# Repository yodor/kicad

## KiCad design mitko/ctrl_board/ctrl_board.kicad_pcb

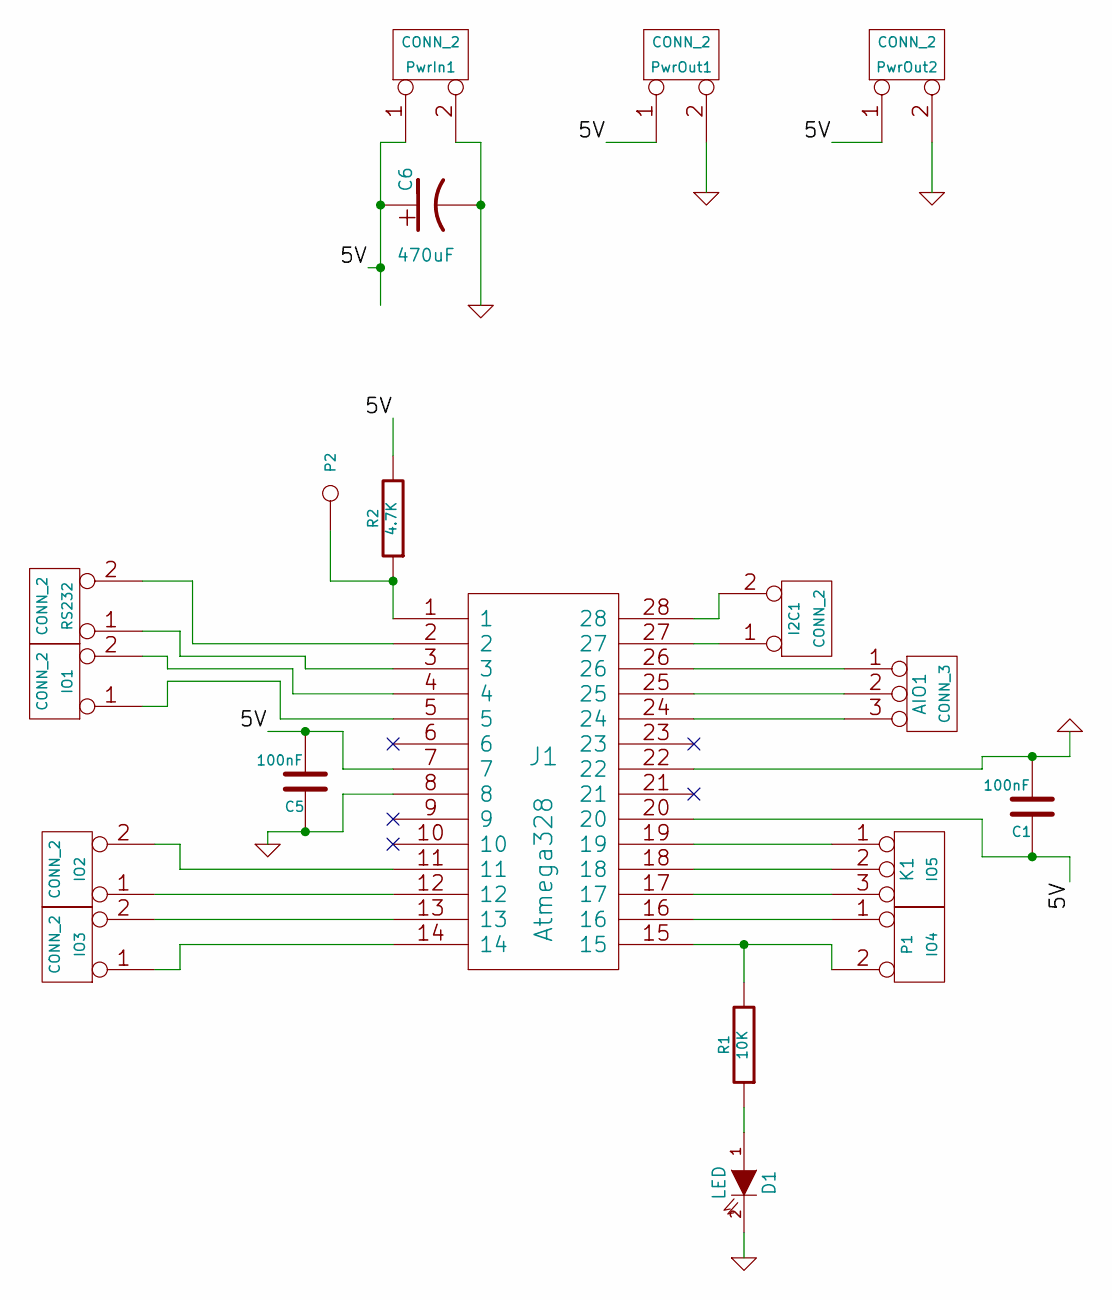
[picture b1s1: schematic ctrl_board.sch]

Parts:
AIO1: CONN_3
C1, C5: 100nF
C6: 470uF
D1: LED
I2C1: CONN_2
IO1, IO2, IO3: CONN_2
J1: Atmega328
K1: IO5
P1: IO4
P2: CONN_1
PwrIn1: CONN_2
PwrOut1, PwrOut2: CONN_2
R1: 10K
R2: 4.7K
RS232: CONN_2

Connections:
/5V: C1.1, C5.2, C6.1, J1.7, J1.20, PwrIn1.1, PwrOut1.1, PwrOut2.1, R2.2
GND: C1.2, C5.1, C6.2, D1.2 (K), J1.8, J1.22, PwrIn1.2 (PM), PwrOut1.2 (PM), PwrOut2.2 (PM)
unnamed: I2C1.1, J1.27
unnamed: I2C1.2 (PM), J1.28
unnamed: IO2.2 (PM), J1.11
unnamed: J1.2, RS232.2 (PM)
unnamed: D1.1 (A), R1.1
unnamed: J1.15, P1.2 (PM), R1.2
unnamed: J1.16, P1.1
unnamed: J1.17, K1.3
unnamed: J1.18, K1.2 (PM)
unnamed: J1.19, K1.1
unnamed: J1.1, P2.1, R2.1
unnamed: J1.3, RS232.1
unnamed: IO1.2 (PM), J1.4
unnamed: IO1.1, J1.5
unnamed: IO2.1, J1.12
unnamed: IO3.2 (PM), J1.13
unnamed: IO3.1, J1.14
unnamed: AIO1.1, J1.26
unnamed: AIO1.2 (PM), J1.25
unnamed: AIO1.3, J1.24

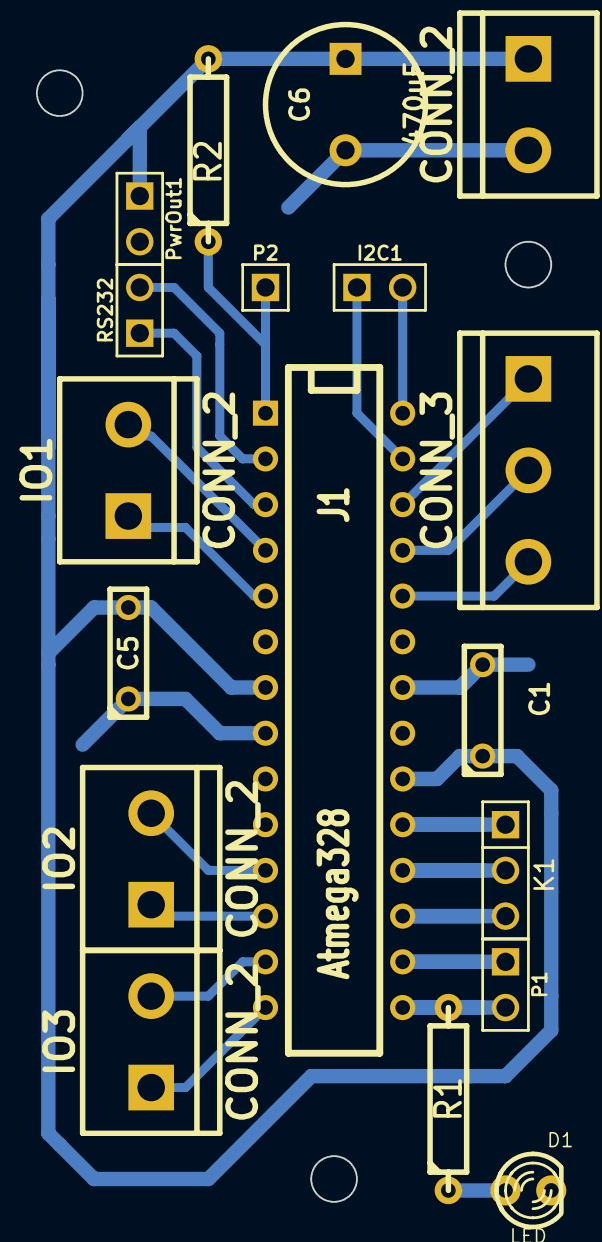
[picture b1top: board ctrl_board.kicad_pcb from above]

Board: 2 copper layers, 28.6 x 62.9 mm, 18 parts (0 on the bottom side), 22 nets.

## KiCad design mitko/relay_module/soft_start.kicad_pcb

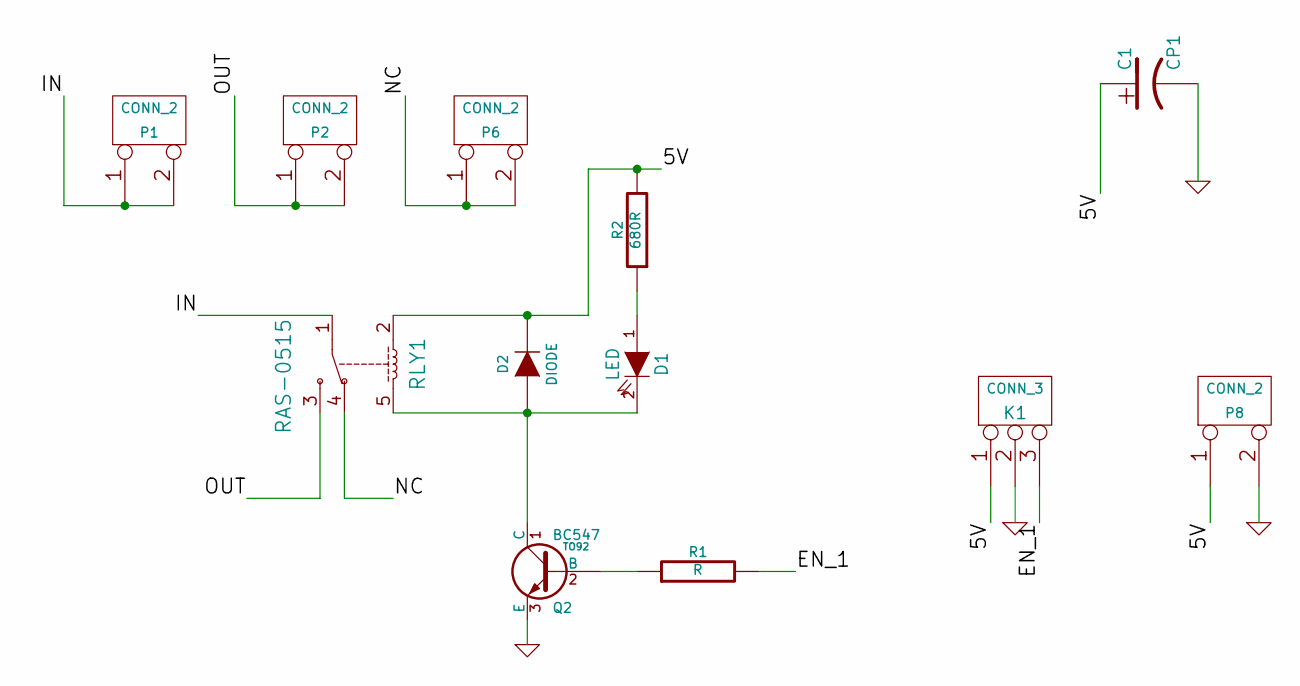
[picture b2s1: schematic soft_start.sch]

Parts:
C1: CP1
D1: LED
D2: DIODE
K1: CONN_3
P1, P2, P6, P8: CONN_2
Q2: BC547; TO92
R1: R
R2: 680R
RLY1: RAS-0515

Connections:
/5V: C1.1, D2.2 (K), K1.1, P8.1, R2.2, RLY1.2
/EN_1: K1.3, R1.2
/IN: P1.1, P1.2 (PM), RLY1.1
/NC: P6.1, P6.2 (PM), RLY1.4
/OUT: P2.1, P2.2 (PM), RLY1.3
GND: C1.2, K1.2 (PM), P8.2 (PM), Q2.3 (E)
unnamed: D1.1 (A), R2.1
unnamed: Q2.2 (B), R1.1
unnamed: D1.2 (K), D2.1 (A), Q2.1 (C), RLY1.5

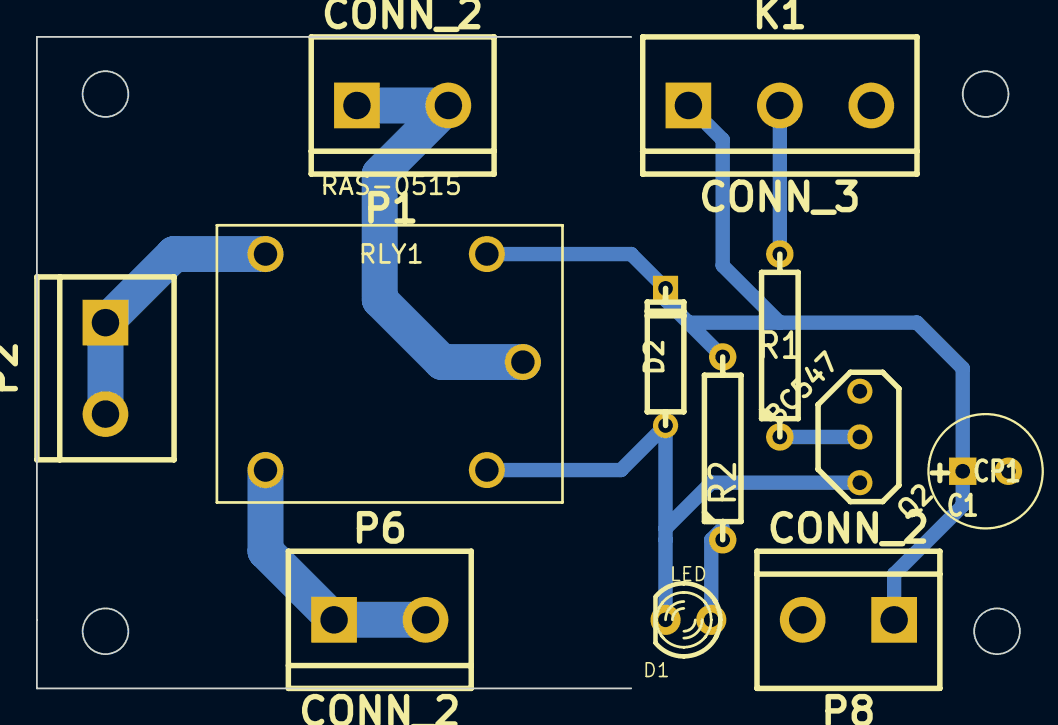
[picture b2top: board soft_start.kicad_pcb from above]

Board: 2 copper layers, 54.6 x 36.2 mm, 12 parts (0 on the bottom side), 9 nets.

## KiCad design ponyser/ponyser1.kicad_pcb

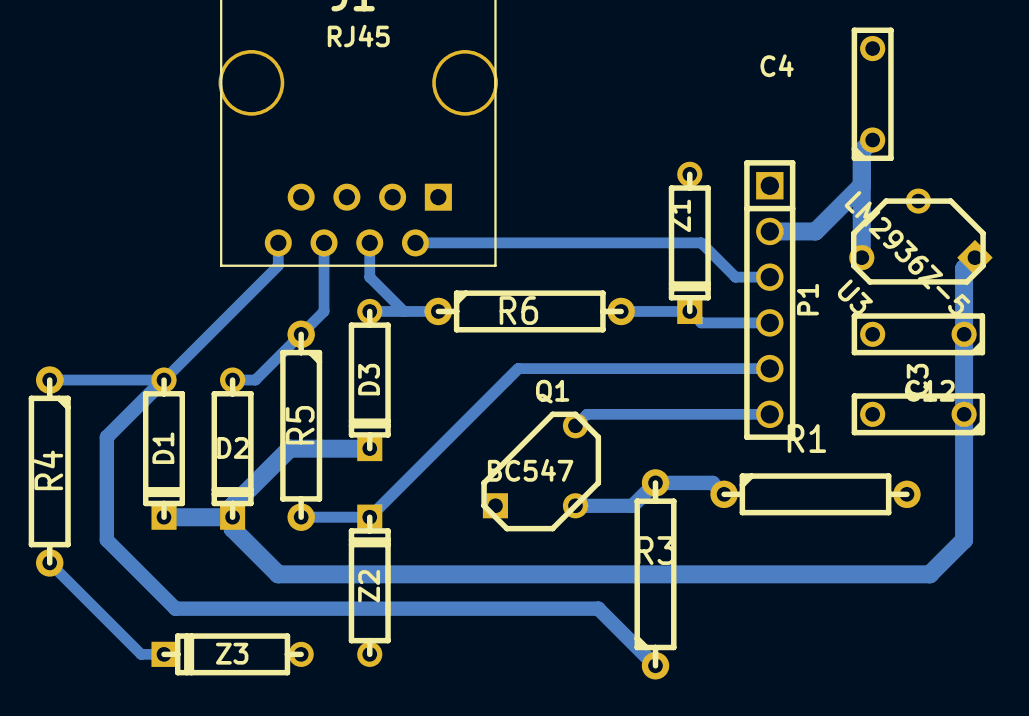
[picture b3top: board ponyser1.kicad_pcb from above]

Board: 2 copper layers, 18 parts (0 on the bottom side), 12 nets.

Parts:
C3, C4: 4.7uF; C2
C12: 100nF; C2
D1, D2, D3: DIODE; D3
J1: RJ45; RJ45_8
P1: CONN_6; PIN_ARRAY-6X1
Q1: BC547; TO92
R1: 15K; R4
R3: 10K; R4
R4, R5, R6: 4.7K; R4
U3: LM2936Z-5; LM78XX-TO92
Z1, Z2, Z3: 5.1V; D3

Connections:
GND: C3.2, C4.2, C12.2, J1.1, P1.1, Q1.1, R1.2, U3.GND, Z1.1, Z2.1, Z3.1
unnamed: Q1.2, R1.1, R3.2
unnamed: P1.5, R5.2, Z2.2
unnamed: R4.2, Z3.2
unnamed: D1.1, J1.8, R3.1, R4.1
unnamed: C3.1, C12.1, D1.2, D2.2, D3.2, U3.VI
unnamed: P1.6, Q1.3
unnamed: D2.1, J1.6, R5.1
unnamed: D3.1, J1.4, R6.1
unnamed: J1.2, P1.3
unnamed: P1.4, R6.2, Z1.2
VCC: C4.1, P1.2, U3.VO

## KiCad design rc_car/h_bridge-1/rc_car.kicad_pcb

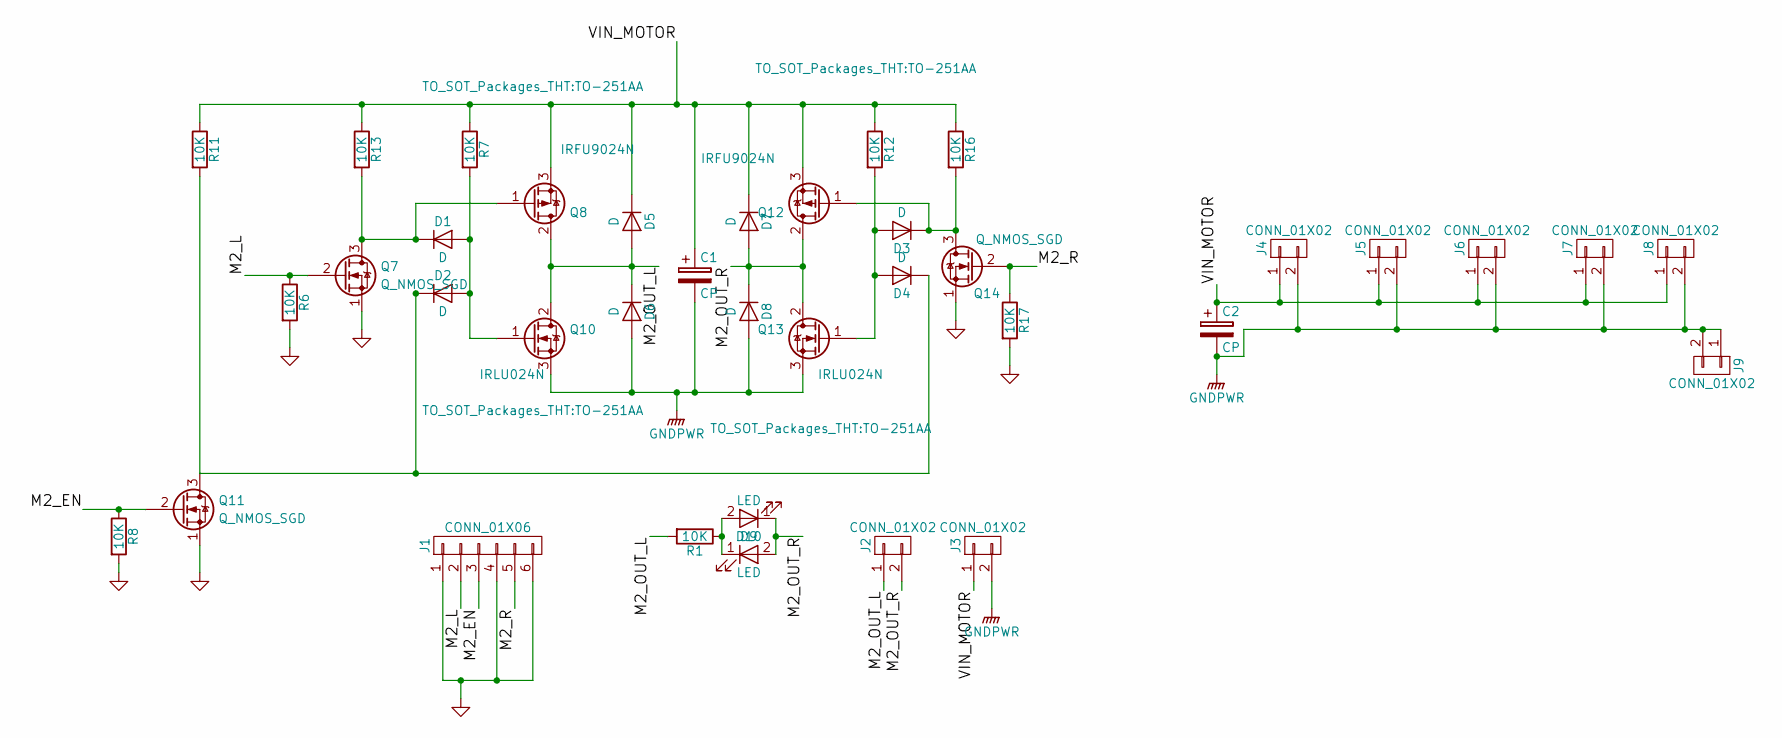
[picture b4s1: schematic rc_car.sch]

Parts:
C1, C2: CP; C_Radial_D8_L11.5_P3.5
D1, D2, D3, D4, D5, D6, D7, D8: D; DO-41
D9, D10: LED; LED-3MM
J1: CONN_01X06; Pin_Header_Straight_1x06
J2, J3, J4, J7, J8, J9: CONN_01X02; bornier2
J5, J6: CONN_01X02; JST_XH_B02B-XH-A_02x2.50mm_Straight
Q7, Q11, Q14: Q_NMOS_SGD; TO-92_Inline_Wide
Q8, Q12: IRFU9024N; TO-251AA
Q10, Q13: IRLU024N; TO-251AA
R1, R6, R8, R17: 10K; R1
R7, R11, R12, R13, R16: 10K; R4

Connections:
/M2_EN: J1.3, Q11.2 (G), R8.1
/M2_L: J1.2, Q7.2 (G), R6.1
/M2_OUT_L: D5.2 (A), D6.1 (K), J2.1, Q8.2 (D), Q10.2 (D), R1.2
/M2_OUT_R: D7.2 (A), D8.1 (K), D9.1 (K), D10.2 (A), J2.2, Q12.2 (D), Q13.2 (D)
/M2_R: J1.5, Q14.2 (G), R17.1
/VIN_MOTOR: C1.1, C2.1, D5.1 (K), D7.1 (K), J3.1, J4.1, J5.1, J6.1, J7.1, J8.1, Q8.3 (S), Q12.3 (S), R7.1, R11.1, R12.1, R13.1, R16.1; also elsewhere on the board
GND: J1.1, J1.4, J1.6, Q7.1 (S), Q11.1 (S), Q14.1 (S), R6.2, R8.2, R17.2
GNDPWR: C1.2, C2.2, D6.2 (A), D8.2 (A), J3.2, J4.2, J5.2, J6.2, J7.2, J8.2, J9.1, J9.2, Q10.3 (S), Q13.3 (S); also elsewhere on the board
unnamed: D1.1 (K), Q7.3 (D), Q8.1 (G), R13.2
unnamed: D1.2 (A), D2.2 (A), Q10.1 (G), R7.2
unnamed: D2.1 (K), D4.1 (K), Q11.3 (D), R11.2
unnamed: D3.1 (K), Q12.1 (G), Q14.3 (D), R16.2
unnamed: D3.2 (A), D4.2 (A), Q13.1 (G), R12.2
unnamed: D9.2 (A), D10.1 (K), R1.1

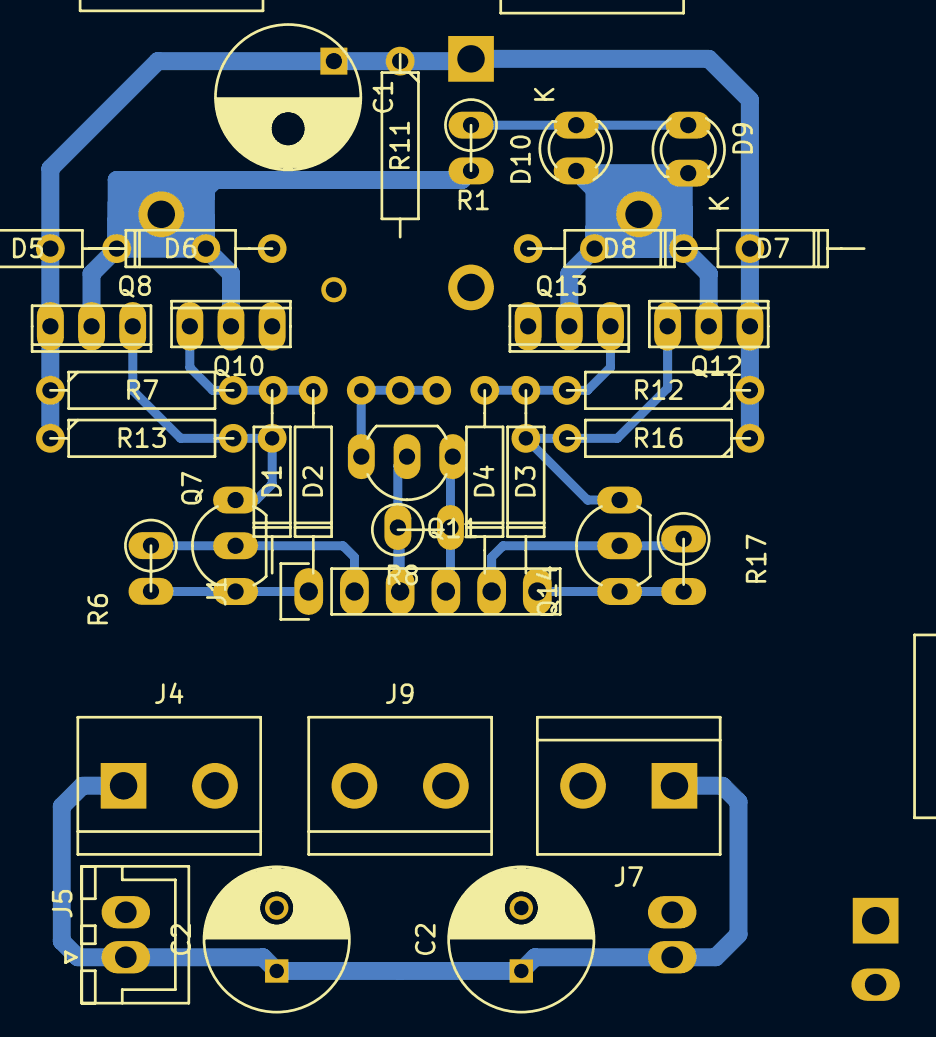
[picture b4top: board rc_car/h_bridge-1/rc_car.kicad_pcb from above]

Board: 2 copper layers, 38 parts (1 on the bottom side), 14 nets.

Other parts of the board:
C2#2: CP; C_Radial_D8_L11.5_P3.5

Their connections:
/VIN_MOTOR: C2#2.1; also elsewhere on the board
GNDPWR: C2#2.2; also elsewhere on the board

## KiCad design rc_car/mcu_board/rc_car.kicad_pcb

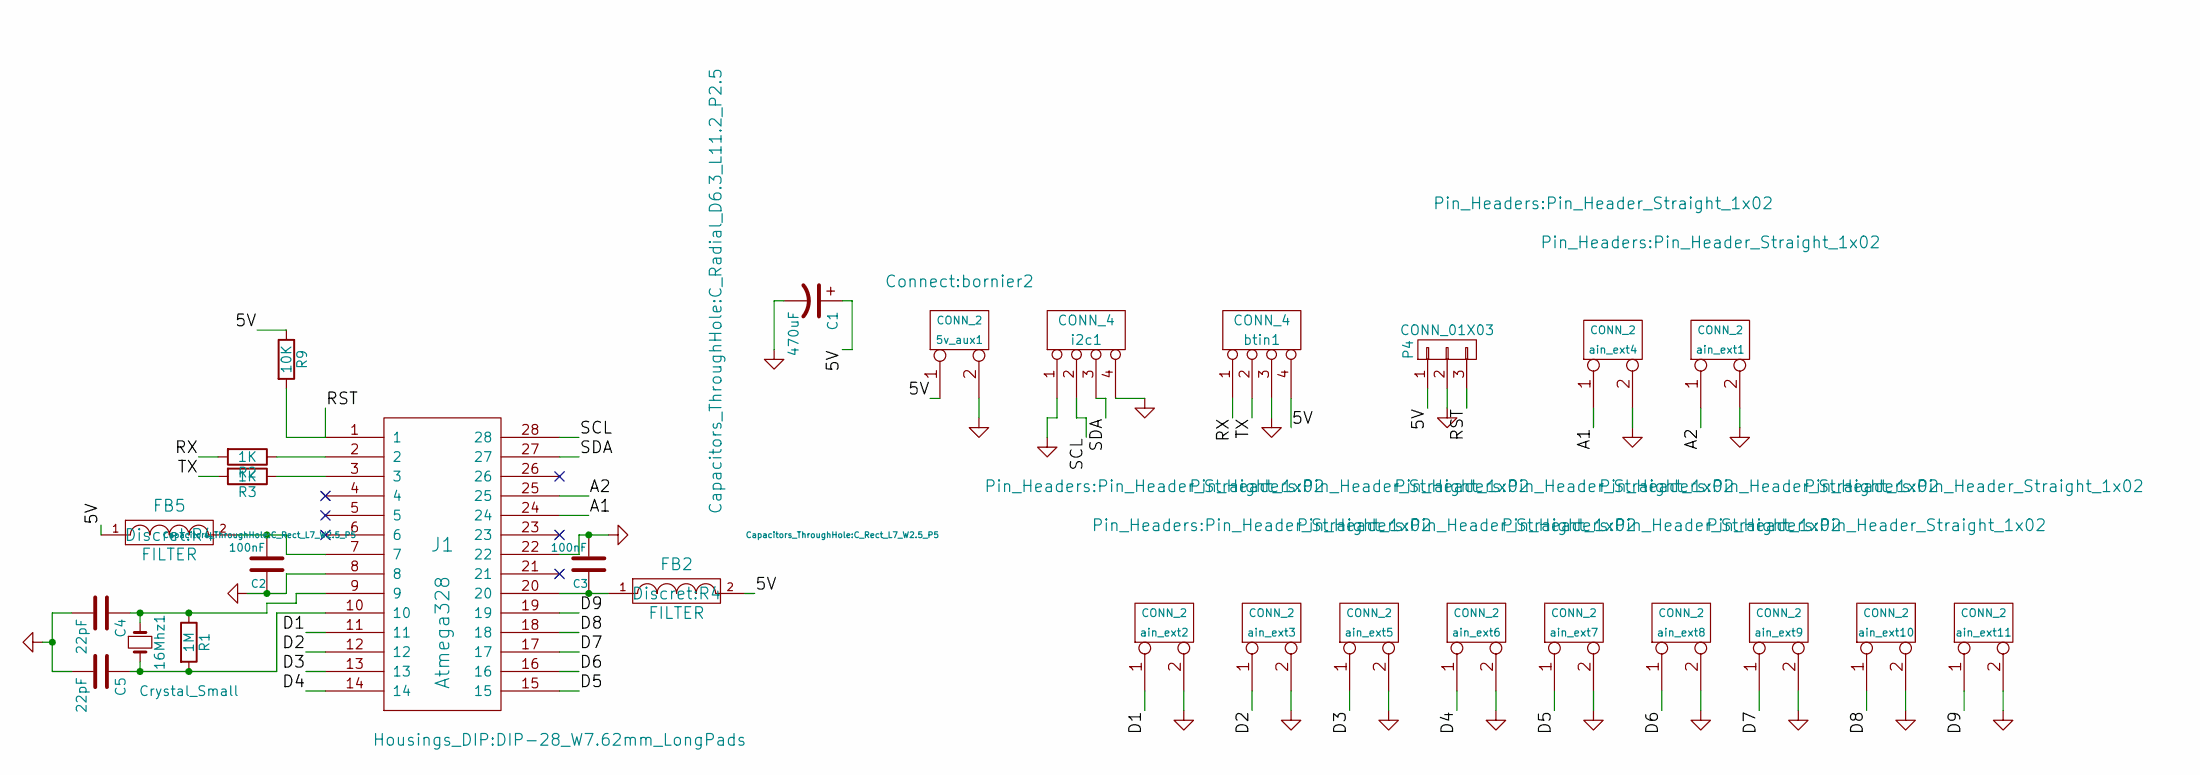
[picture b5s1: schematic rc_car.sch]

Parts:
5v_aux1: CONN_2; bornier2
16Mhz1: Crystal_Small; Crystal_HC49-U_Vertical
C1: 470uF; C_Radial_D6.3_L11.2_P2.5
C2, C3: 100nF; C_Rect_L7_W2.5_P5
C4, C5: 22pF; C_Disc_D3_P2.5
FB2, FB5: FILTER; R4
J1: Atmega328; DIP-28_W7.62mm_LongPads
P4: CONN_01X03; Pin_Header_Straight_1x03
R1: 1M; R1
R2, R3: 1K; R1
R9: 10K; R1
ain_ext1, ain_ext2, ain_ext3, ain_ext4, ain_ext5, ain_ext6, ain_ext7, ain_ext8, ain_ext9, ain_ext10, ain_ext11: CONN_2; Pin_Header_Straight_1x02
btin1: CONN_4; Pin_Header_Straight_1x04
i2c1: CONN_4; Pin_Header_Straight_1x04

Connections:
/5V: 5v_aux1.1, C1.1, FB2.2, FB5.1, P4.1, R9.1, btin1.4
/A1: J1.24, ain_ext4.1
/A2: J1.25, ain_ext1.1
/D1: J1.11, ain_ext2.1
/D2: J1.12, ain_ext3.1
/D3: J1.13, ain_ext5.1
/D4: J1.14, ain_ext6.1
/D5: J1.15, ain_ext7.1
/D6: J1.16, ain_ext8.1
/D7: J1.17, ain_ext9.1
/D8: J1.18, ain_ext10.1
/D9: J1.19, ain_ext11.1
/RST: J1.1, P4.3, R9.2
/RX: R2.2, btin1.1
/SCL: J1.28, i2c1.2
/SDA: J1.27, i2c1.3
/TX: R3.2, btin1.2
GND: 5v_aux1.2 (PM), C1.2, C2.1, C3.2, C4.2, C5.2, J1.8, J1.22, P4.2, ain_ext1.2 (PM), ain_ext2.2 (PM), ain_ext3.2 (PM), ain_ext4.2 (PM), ain_ext5.2 (PM), ain_ext6.2 (PM), ain_ext7.2 (PM), ain_ext8.2 (PM), ain_ext9.2 (PM), ain_ext10.2 (PM), ain_ext11.2 (PM), btin1.3, i2c1.1, i2c1.4
unnamed: 16Mhz1.1, C4.1, J1.9, R1.1
unnamed: 16Mhz1.2, C5.1, J1.10, R1.2
unnamed: C2.2, FB5.2, J1.7
unnamed: C3.1, FB2.1, J1.20
unnamed: J1.2, R2.1
unnamed: J1.3, R3.1

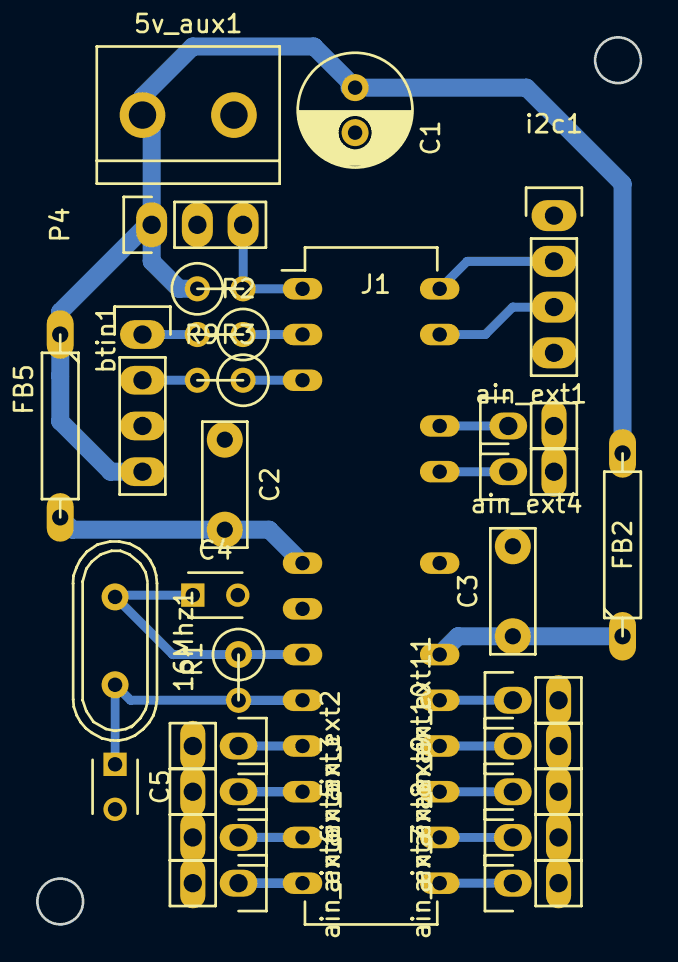
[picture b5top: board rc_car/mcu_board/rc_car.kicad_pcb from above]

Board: 2 copper layers, 33.5 x 49.3 mm, 28 parts (0 on the bottom side), 24 nets.
